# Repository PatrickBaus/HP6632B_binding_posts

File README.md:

# HP 66332A and HP 6632B-6634B Frontpanel Binding Post PCB
This repository contains the schematics for a PCB to mount frontpanel binding post on an [HP 6632B](https://www.keysight.com/us/en/product/6632B/100-watt-system-power-supply-20v-5a.html) (and siblings) power supply. It is an adaption of the original A4 PCB used in option #020 units.

## Contents
- [Introduction](#introduction)
- [Design Files](#design-files)
- [Related Repositories](#related-repositories)
- [Versioning](#versioning)
- [License](#license)

## Introduction
In addition to the original option #20 PCB, this board breaks out the sense connections as well and also the chassis ground. This makes connecting multiple [HP 663xB](https://www.keysight.com/us/en/product/6632B/100-watt-system-power-supply-20v-5a.html) in parallel possible. On the downside, this requires connecting the sense pins externally. To make this easier I also made a small [shorting bar](https://github.com/PatrickBaus/HP6632B_shorting_bar) to easily short the sense terminals to the force terminals directly at the power supply output.

The components chosen allow the board to be used on all variants of the HP 663xB family - even the 100 V 6634B. A variety of different binding posts can be used. There are HP/Agilent versions available on Ebay. I used [Pomona 4243-0](https://www.pomonaelectronics.com/products/hardware/double-binding-post) ([Digikey](https://www.digikey.de/product-detail/de/pomona-electronics/4243-0/501-1126-ND/604321)) and [3760-5](https://www.pomonaelectronics.com/products/hardware/binding-post-tin-plated) ([Digikey](https://www.digikey.de/product-detail/de/pomona-electronics/3760-5/501-1506-ND/736554)) binding posts.

The final result looks like this:

## Design Files
The root folder contains the KiCAD files. The bill of materials can be found on the [releases](../../releases) page along with Gerber files for production.

## Related Repositories
See the following repositories which contain addional optional parts.

- [HP 66332A and HP 6632B-6634B Shorting Bar](https://github.com/PatrickBaus/HP6632B_shorting_bar)

## Versioning
I use [SemVer](http://semver.org/) for versioning. For the versions available, see the [tags](../../tags) available for this repository.

- MAJOR versions in this context mean a breaking change to the external interface of the hardware like different connectors or functions.
- MINOR versions contain changes to the hardware that only affect the inner workings of the circuit, but otherwise the performance is unaffected.
- PATCH versions do not affect the schematics or invalidate older bill of materials. These changes may include updated components (to replace obsolete parts for example), an updated silkscreen, or fixed typos.

## License
This work is released under the CERN-OHL-W
See [https://ohwr.org/cern_ohl_w_v2.pdf](https://ohwr.org/cern_ohl_w_v2.pdf) or the included LICENSE file for more information.

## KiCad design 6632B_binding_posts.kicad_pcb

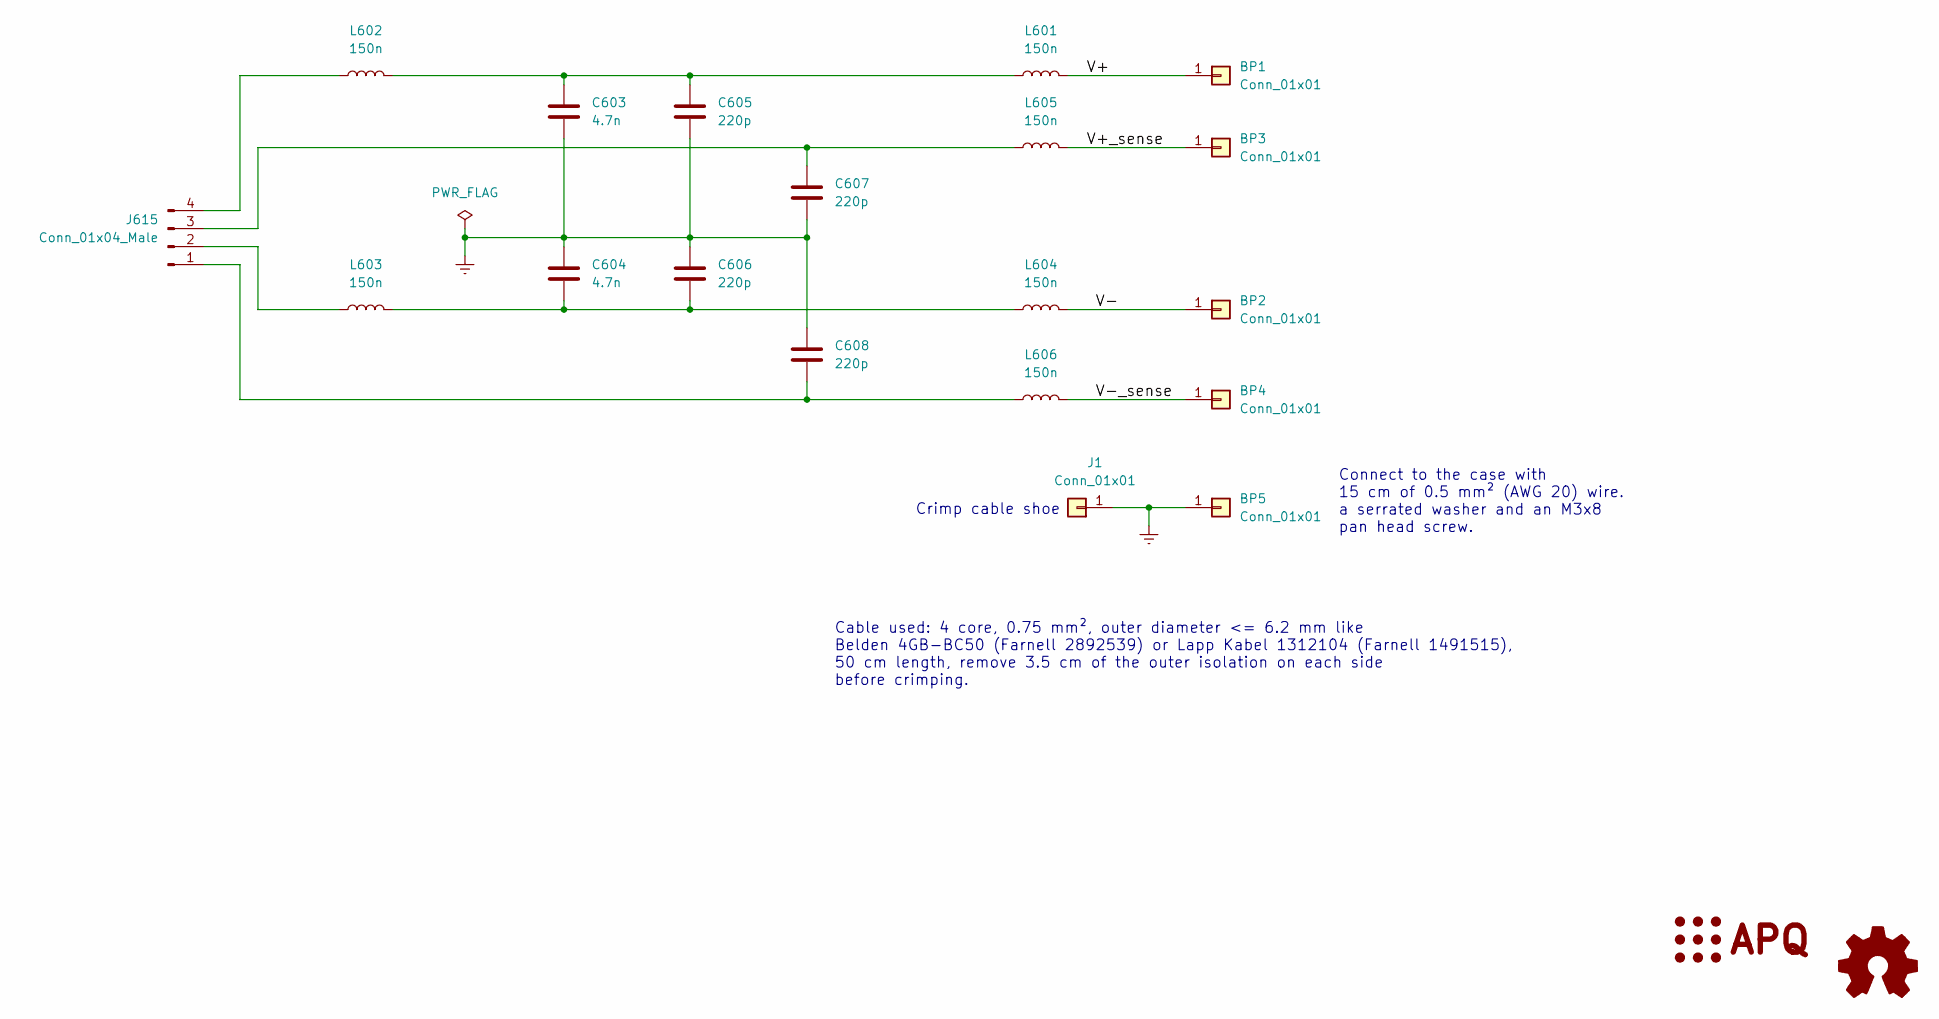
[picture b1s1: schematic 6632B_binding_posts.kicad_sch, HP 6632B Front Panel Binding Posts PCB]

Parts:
BP1, BP2, BP3, BP4, BP5: Conn_01x01; TestPoint_Keystone_5019_Minature
C603, C604: 4.7n; C_Rect_L13.0mm_W5.0mm_P10.00mm_FKS3_FKP3_MKS4
C605, C606, C607, C608: 220p; C_Disc_D6.0mm_W4.4mm_P5.00mm
J1: Conn_01x01; TestPoint_THTPad_D3.0mm_Drill1.5mm
J615: Conn_01x04_Male; Molex_KK-396_A-41791-0004_1x04_P3.96mm_Vertical
L601, L602, L603, L604, L605, L606: 150n; L_1008_2520Metric
LOGO1: Logo_Open_Hardware_Small; OSHW-Logo_7.5x8mm_SilkScreen
LOGO2: Logo_APQ; APQ-Logo_small

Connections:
/V+: BP1.1, L601.2
/V+_sense: BP3.1, L605.2
/V-: BP2.1, L604.2
/V-_sense: BP4.1, L606.2
Earth: BP5.1, C603.2, C604.1, C605.2, C606.1, C607.2, C608.1, J1.1
unnamed: C603.1, C605.1, L601.1, L602.2
unnamed: C604.2, C606.2, L603.2, L604.1
unnamed: C608.2, J615.1, L606.1
unnamed: J615.2, L603.1
unnamed: C607.1, J615.3, L605.1
unnamed: J615.4, L602.1

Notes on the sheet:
Crimp cable shoe
Connect to the case with 15 cm of 0.5 mm² (AWG 20) wire. a serrated washer and an M3x8 pan head screw.
Cable used: 4 core, 0.75 mm², outer diameter <= 6.2 mm like Belden 4GB-BC50 (Farnell 2892539) or Lapp Kabel 1312104 (Farnell 1491515), 50 cm length, remove 3.5 cm of the outer isolation on each side before crimping.

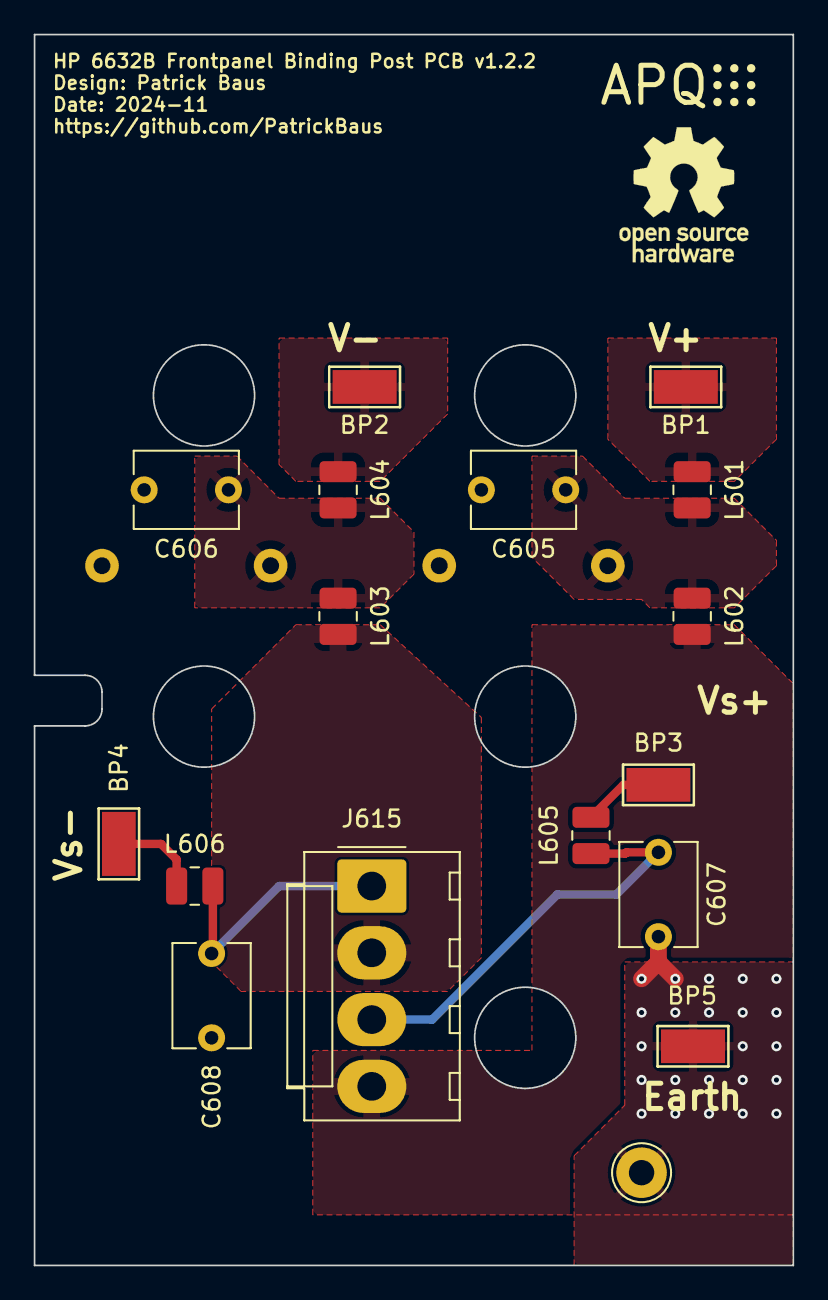
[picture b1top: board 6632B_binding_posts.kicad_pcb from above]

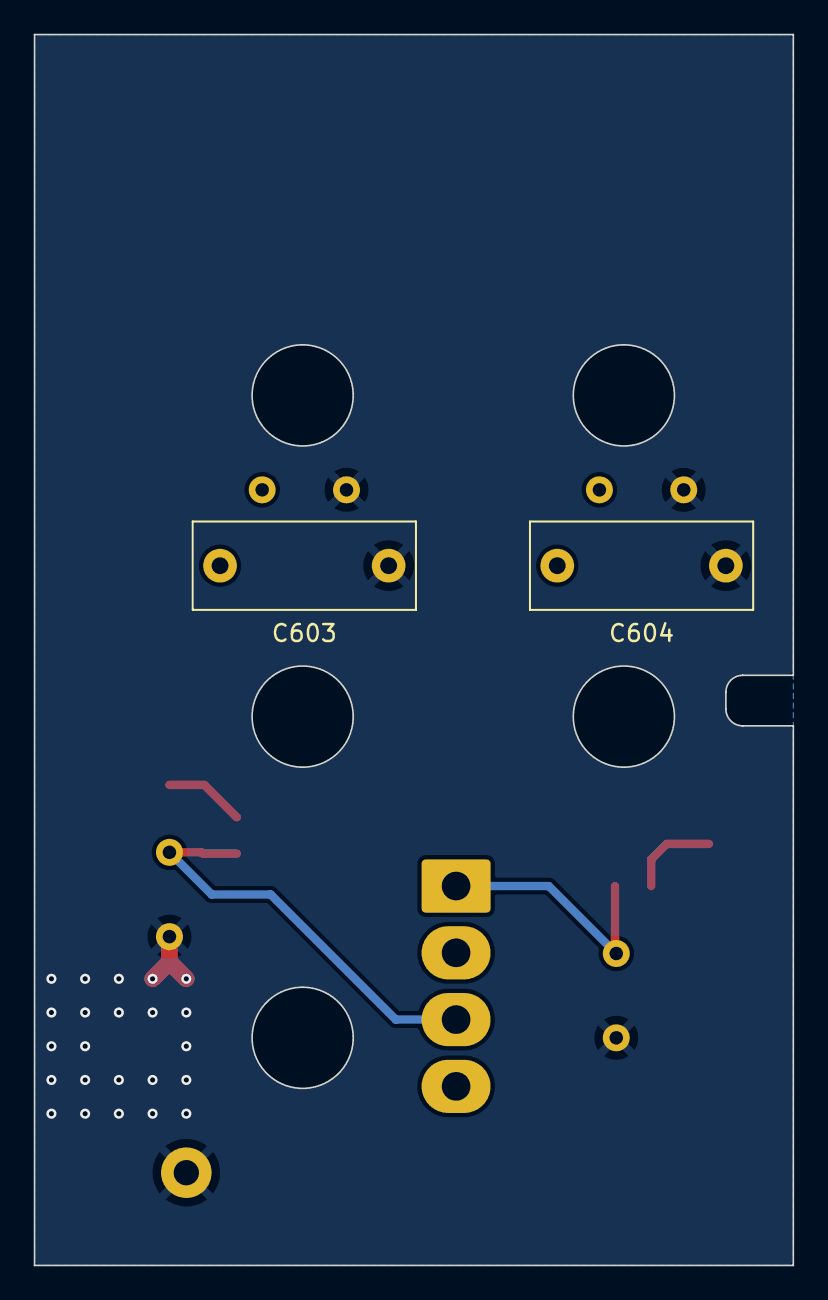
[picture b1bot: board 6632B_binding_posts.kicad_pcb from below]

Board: 2 copper layers, 45.0 x 73.0 mm, 21 parts (2 on the bottom side), 11 nets.

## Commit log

2020-10-23 Updated to v1.1 Moved cutout 1.5 mm down Decreased size of earth connection J1
2020-10-23 Added readme Added binding posts to the BOM
2020-10-23 Update README.md
    Fixed typo in link
2020-10-23 Added BOM and costs file
2020-10-23 Added missing crimp connector
2020-10-23 Update README.md
    Fixed typo
2021-07-02 Increased GND plane clearance to 0.25 mm
2024-11-14 Increased drill hole size for the Earth solder connection
2024-11-14 Update to KiCad 8
2024-11-14 Updated license
2024-11-14 Renamed source files
2024-11-14 Drop git submodule
2024-11-14 Update logo
2024-11-14 Add CI
2024-11-14 Bump version to 1.1.2
2024-11-14 Reformat version string
2024-11-14 Add more links
2024-11-15 Update dependabot.yml
    Remove unused submodule check
2024-11-15 Fixed image label
2024-11-15 Added shorting bar link to readme
2024-11-15 Fix permission issue when uploading the design files
2026-04-29 [gha] Bump actions/upload-artifact from 4 to 7
    Bumps [actions/upload-artifact](https://github.com/actions/upload-artifact) from 4 to 7.
    - [Release notes](https://github.com/actions/upload-artifact/releases)
    - [Commits](https://github.com/actions/upload-artifact/compare/v4...v7)
    ---
    updated-dependencies:
    - dependency-name: actions/upload-artifact
2026-04-29 [gha] Bump actions/download-artifact from 4 to 8
    Bumps [actions/download-artifact](https://github.com/actions/download-artifact) from 4 to 8.
    - [Release notes](https://github.com/actions/download-artifact/releases)
    - [Commits](https://github.com/actions/download-artifact/compare/v4...v8)
    ---
    updated-dependencies:
    - dependency-name: actions/download-artifact
2026-04-29 [gha] Bump actions/checkout from 4 to 6
    Bumps [actions/checkout](https://github.com/actions/checkout) from 4 to 6.
    - [Release notes](https://github.com/actions/checkout/releases)
    - [Changelog](https://github.com/actions/checkout/blob/main/CHANGELOG.md)
    - [Commits](https://github.com/actions/checkout/compare/v4...v6)
    ---
    updated-dependencies:
2026-06-18 [gha] Bump actions/checkout from 6 to 7
    Bumps [actions/checkout](https://github.com/actions/checkout) from 6 to 7.
    - [Release notes](https://github.com/actions/checkout/releases)
    - [Changelog](https://github.com/actions/checkout/blob/main/CHANGELOG.md)
    - [Commits](https://github.com/actions/checkout/compare/v6...v7)
    ---
    updated-dependencies:

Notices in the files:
6632B_binding_posts.kicad_pcb:
Copyright (©) 2024, Patrick Baus
Licensed under CERN OHL-W v2.0
